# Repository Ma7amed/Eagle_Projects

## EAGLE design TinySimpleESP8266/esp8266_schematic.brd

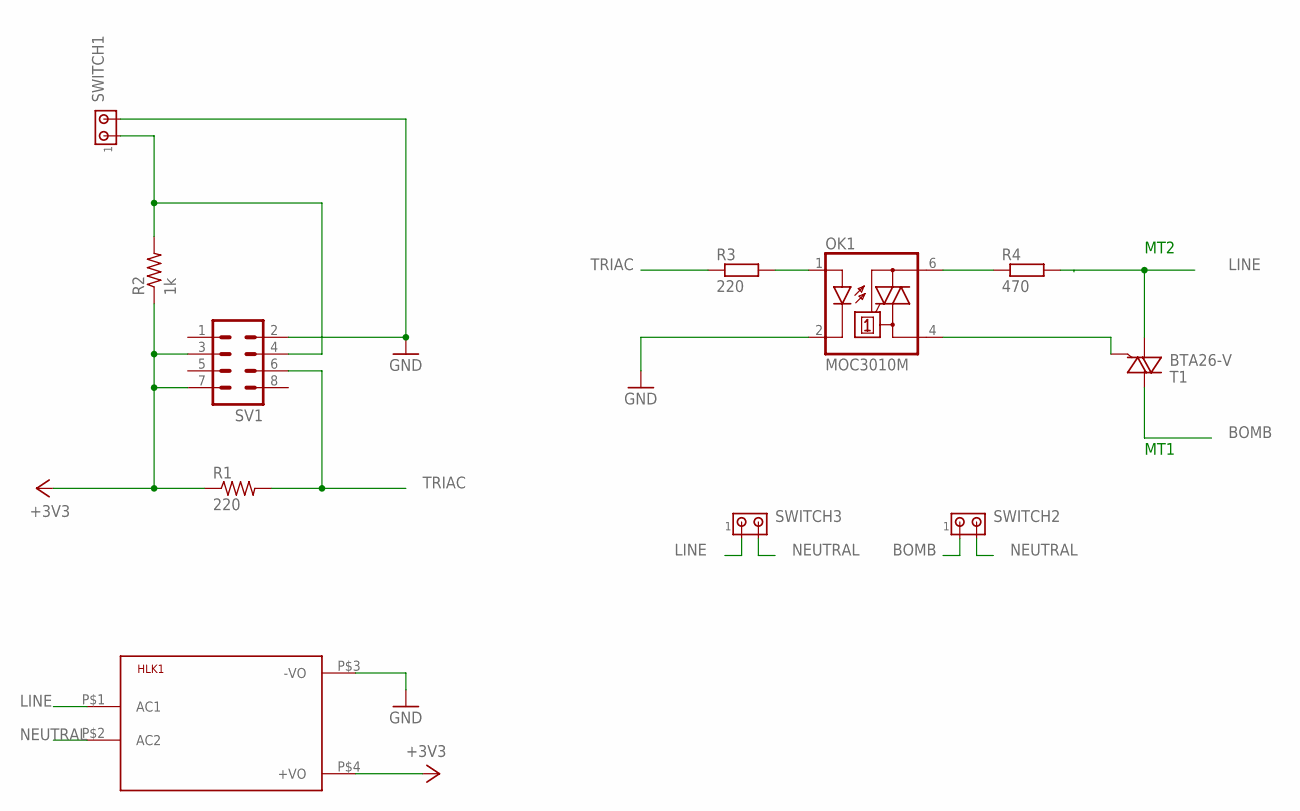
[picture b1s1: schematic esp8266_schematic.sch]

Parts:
HLK1: HLK-PM013W; HLK-PM01
OK1: MOC3010M; DIL06
R1: 220; 0207/2V
R2: 1k; 0207/2V
R3: 220; 0204/5
R4: 470; 0207/15
SV1: MA04-2
SWITCH1, SWITCH2, SWITCH3: MTA02-100; 10X02MTA
T1: BTA26-V; TOP3S-1

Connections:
+3V3: HLK1.P$4 (+VO), R1.1, R2.1, SV1.3, SV1.7
BOMB: SWITCH2.1, T1.A2
GND: HLK1.P$3 (-VO), OK1.2 (C), SV1.2, SWITCH1.2
LINE: HLK1.P$1 (AC1), R4.2, SWITCH3.1, T1.A1
unnamed: OK1.1 (A), R3.2
unnamed: R2.2, SV1.4, SWITCH1.1
unnamed: OK1.6 (A2), R4.1
unnamed: OK1.4 (A1), T1.G
NEUTRAL: HLK1.P$2 (AC2), SWITCH2.2, SWITCH3.2
TRIAC: R1.2, R3.1, SV1.6

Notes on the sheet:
MT2
MT1

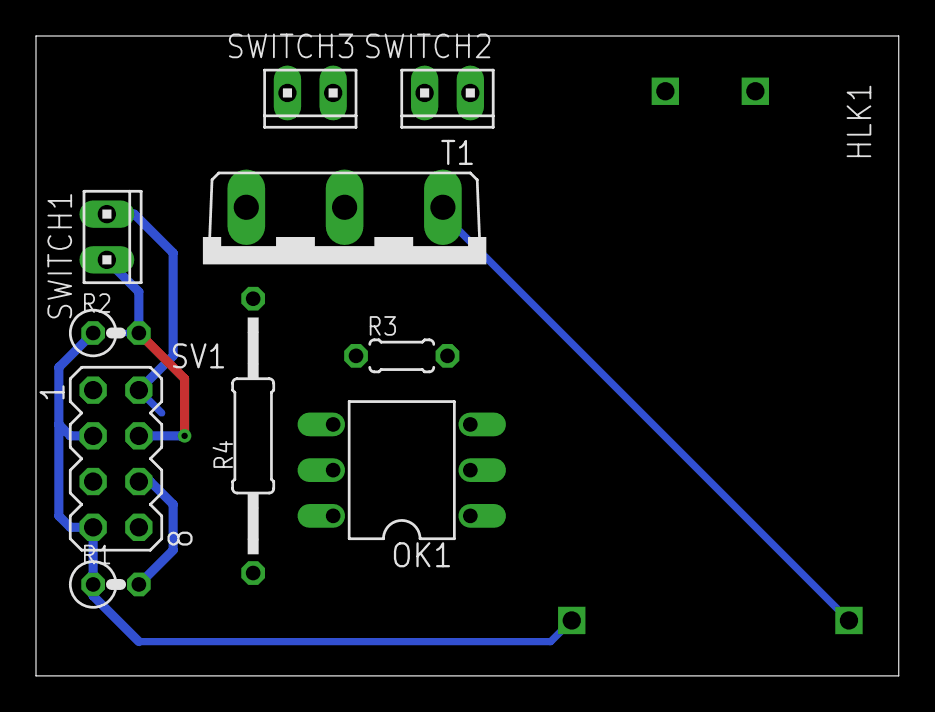
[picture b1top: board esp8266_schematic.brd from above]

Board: 2 copper layers, 47.9 x 35.6 mm, 11 parts (0 on the bottom side), 10 nets.

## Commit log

2019-08-25 initial
    Test
